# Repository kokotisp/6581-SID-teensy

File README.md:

# 6581-SID-teensy
Dual 6581 SID Emulator using teensy 3.6

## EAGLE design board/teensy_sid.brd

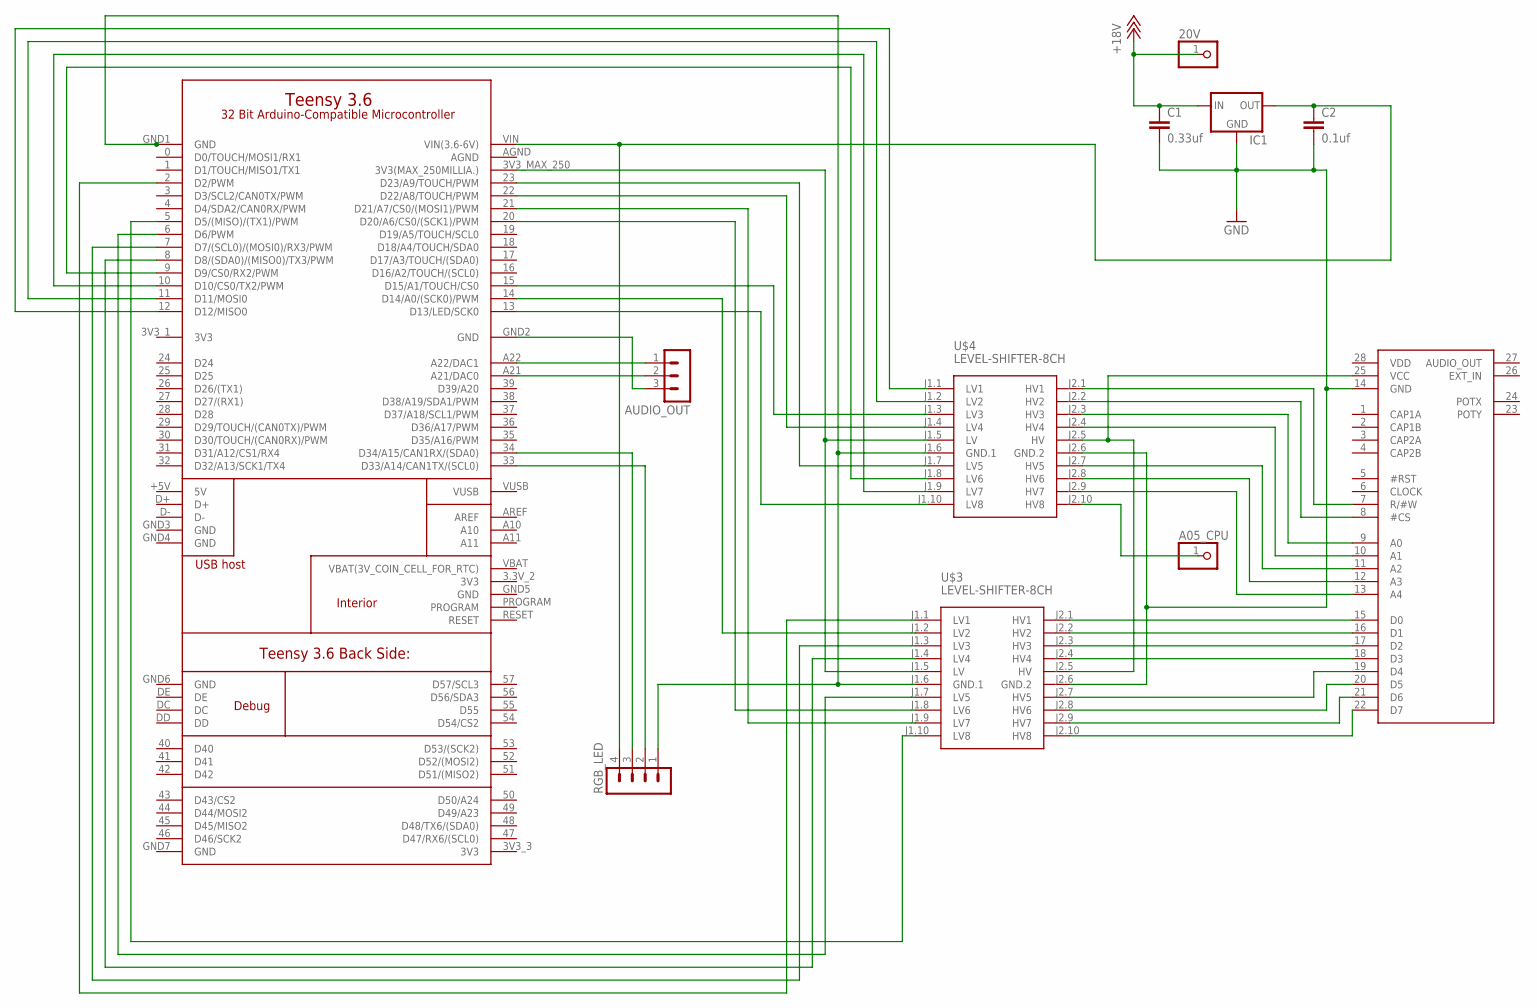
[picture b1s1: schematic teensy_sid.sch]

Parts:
20V: PINHD-1X1; 1X01
A05_CPU: PINHD-1X1; 1X01
AUDIO_OUT: MA03-1
C1: 0.33uf; C025-024X044
C2: 0.1uf; C025-024X044
IC1: 78XXL
RGB_LED: MA04-1
U$1: SID_6581; DIL28-6
U$2: TEENSY-3.6_FULL
U$3, U$4: LEVEL-SHIFTER-8CH

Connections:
3V3: U$2.3V3_1 (3V3)
+18V: 20V.1, C1.1, IC1.IN
A0: U$1.9 (A0), U$4.J2.3 (HV3)
A1: U$1.10 (A1), U$4.J2.4 (HV4)
A2: U$1.11 (A2), U$4.J2.7 (HV5)
A3: U$1.12 (A3), U$4.J2.8 (HV6)
A4: U$1.13 (A4), U$4.J2.9 (HV7)
AGND: U$2.AGND
CS#: U$1.8 (#CS), U$4.J2.2 (HV2)
D0: U$1.15 (D0), U$3.J2.1 (HV1)
D1: U$1.16 (D1), U$3.J2.2 (HV2)
D2: U$1.17 (D2), U$3.J2.3 (HV3)
D3: U$1.18 (D3), U$3.J2.4 (HV4)
D4: U$1.19 (D4), U$3.J2.7 (HV5)
D5: U$1.20 (D5), U$3.J2.8 (HV6)
D6: U$1.21 (D6), U$3.J2.9 (HV7)
D7: U$1.22 (D7), U$3.J2.10 (HV8)
GND: C1.2, C2.2, IC1.GND, U$1.14 (GND), U$3.J2.6 (GND.2), U$4.J2.6 (GND.2)
unnamed: U$2.12 (D12/MISO0), U$4.J1.1 (LV1)
unnamed: U$2.11 (D11/MOSI0), U$4.J1.2 (LV2)
unnamed: U$2.15 (D15/A1/TOUCH/CS0), U$4.J1.3 (LV3)
unnamed: AUDIO_OUT.2, U$2.A21 (A21/DAC0)
unnamed: AUDIO_OUT.1, U$2.A22 (A22/DAC1)
unnamed: U$2.13 (D13/LED/SCK0), U$4.J1.10 (LV8)
unnamed: U$2.9 (D9/CS0/RX2/PWM), U$4.J1.8 (LV6)
unnamed: AUDIO_OUT.3, U$2.GND2 (GND)
unnamed: U$2.3V3_MAX_250 (3V3(MAX_250MILLIA.)), U$3.J1.5 (LV), U$4.J1.5 (LV)
unnamed: U$2.20 (D20/A6/CS0/(SCK1)/PWM), U$3.J1.8 (LV6)
unnamed: U$2.21 (D21/A7/CS0/(MOSI1)/PWM), U$3.J1.9 (LV7)
unnamed: U$2.2 (D2/PWM), U$3.J1.1 (LV1)
unnamed: U$2.22 (D22/A8/TOUCH/PWM), U$4.J1.4 (LV4)
unnamed: U$2.7 (D7/(SCL0)/(MOSI0)/RX3/PWM), U$3.J1.3 (LV3)
unnamed: A05_CPU.1, U$4.J2.10 (HV8)
unnamed: U$2.8 (D8/(SDA0)/(MISO0)/TX3/PWM), U$3.J1.4 (LV4)
unnamed: U$2.6 (D6/PWM), U$3.J1.7 (LV5)
unnamed: C2.1, IC1.OUT, RGB_LED.4, U$2.VIN (VIN(3.6-6V))
unnamed: U$2.5 (D5/(MISO)/(TX1)/PWM), U$3.J1.10 (LV8)
unnamed: U$1.25 (VCC), U$3.J2.5 (HV), U$4.J2.5 (HV)
unnamed: RGB_LED.1, U$2.GND1 (GND), U$3.J1.6 (GND.1), U$4.J1.6 (GND.1)
unnamed: U$2.14 (D14/A0/(SCK0)/PWM), U$3.J1.2 (LV2)
unnamed: U$2.23 (D23/A9/TOUCH/PWM), U$4.J1.7 (LV5)
unnamed: U$2.10 (D10/CS0/TX2/PWM), U$4.J1.9 (LV7)
unnamed: RGB_LED.3, U$2.34 (D34/A15/CAN1RX/(SDA0))
unnamed: RGB_LED.2, U$2.33 (D33/A14/CAN1TX/(SCL0))
RW#: U$1.7 (R/#W), U$4.J2.1 (HV1)

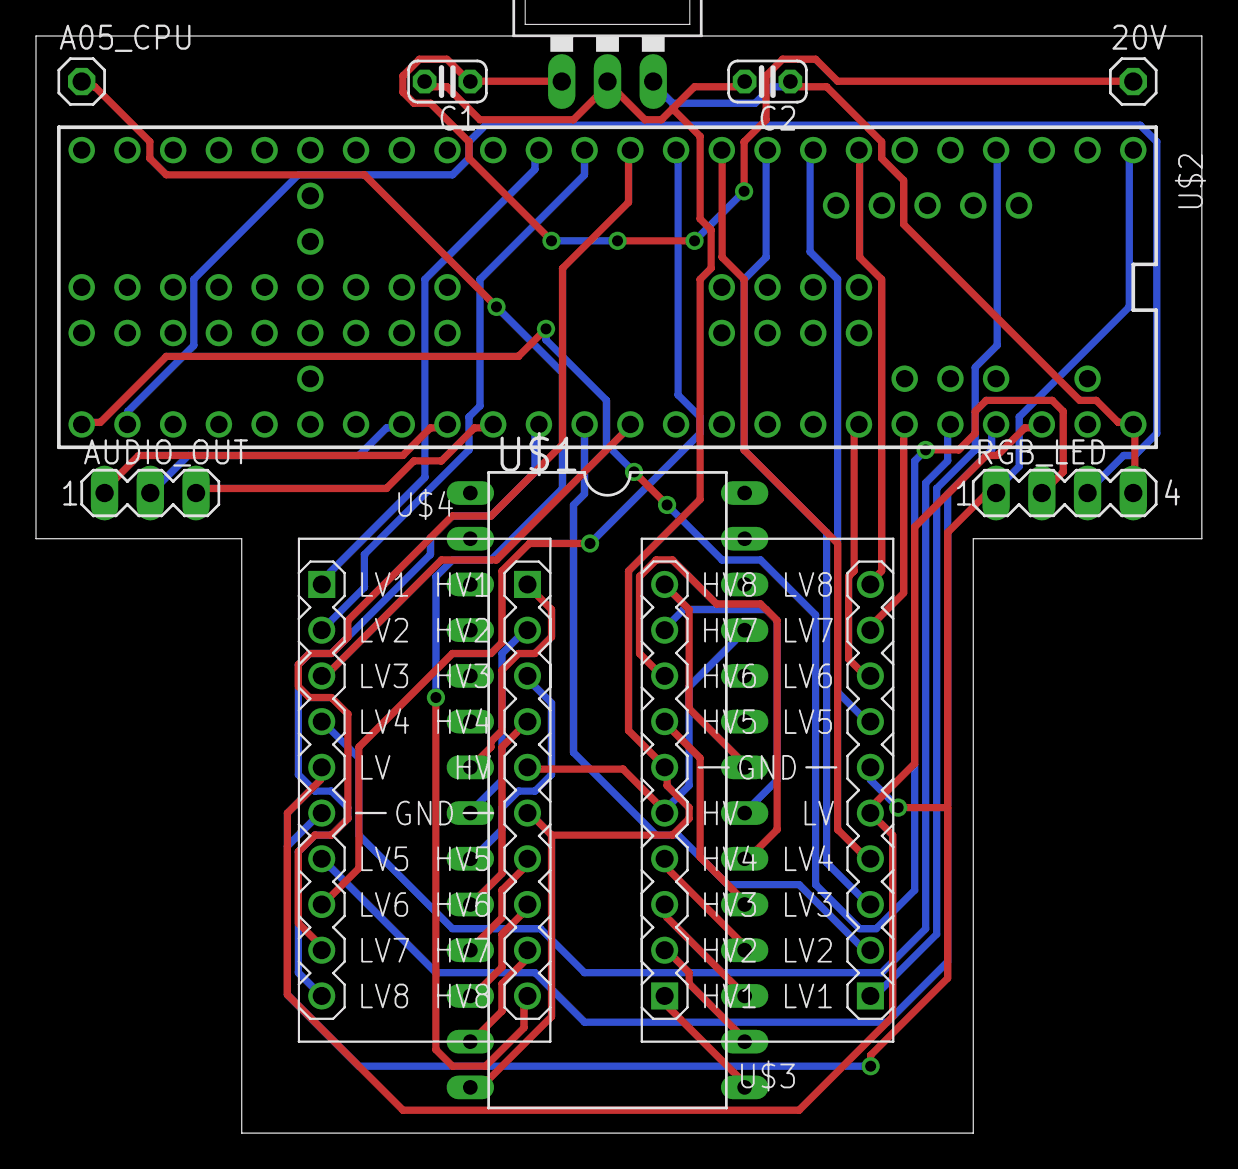
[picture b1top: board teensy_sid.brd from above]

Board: 2 copper layers, 64.8 x 61.0 mm, 11 parts (0 on the bottom side), 43 nets.

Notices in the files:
parts and their libraries:
diy-modules: Released under the Creative Commons Attribution 4.0 International License: http://creativecommons.org/licenses/by/4.0
